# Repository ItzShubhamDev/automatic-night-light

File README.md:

# Auto Night Light

An set of automatic lights that turns on and off automatically according to environment lighting.

## Schematic

## PCB

## 3D Images

## Bill Of Materials

| Name                 | Quantity |
| -------------------- | -------- |
| Battery Cell CR2032  | 1        |
| LED 5mm              | 5        |
| Transistor 2N3904    | 1        |
| Photoresistor GL5528 | 1        |
| Resistor 220Ω        | 1        |
| Resistor 47kΩ        | 1        |
| Push Button 6mm      | 1        |

Made by [@Shubham](https://hackclub.slack.com/team/U07FW3J47ME)!

Made as a part of [Solder YSWS](http://solder.hackclub.com/)!

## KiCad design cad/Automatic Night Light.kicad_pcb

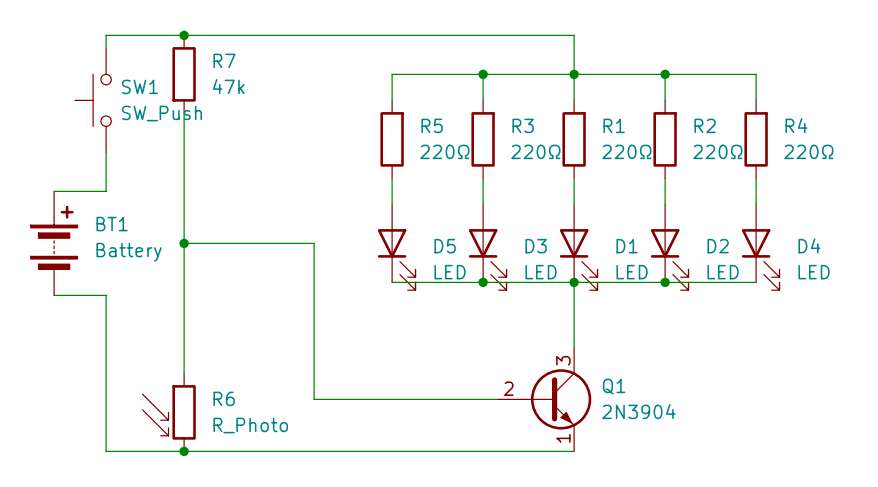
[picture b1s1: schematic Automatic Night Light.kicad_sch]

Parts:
BT1: Battery; BatteryHolder_Keystone_3034_1x20mm
D1, D2, D3, D4, D5: LED; LED_D5.0mm
Q1: 2N3904; TO-92_Inline
R1, R2, R3, R4, R5: 220Ω; R_Axial_DIN0207_L6.3mm_D2.5mm_P7.62mm_Horizontal
R6: R_Photo; R_LDR_7x6mm_P5.1mm_Vertical
R7: 47k; R_Axial_DIN0207_L6.3mm_D2.5mm_P7.62mm_Horizontal
SW1: SW_Push; SW_PUSH_6mm

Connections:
unnamed: BT1.1 (+), SW1.1
unnamed: BT1.2 (-), Q1.1 (E), R6.2
unnamed: D1.2 (A), R1.1
unnamed: D1.1 (K), D2.1 (K), D3.1 (K), D4.1 (K), D5.1 (K), Q1.3 (C)
unnamed: D2.2 (A), R2.1
unnamed: D3.2 (A), R3.1
unnamed: D4.2 (A), R4.1
unnamed: D5.2 (A), R5.1
unnamed: Q1.2 (B), R6.1, R7.2
unnamed: R1.2, R2.2, R3.2, R4.2, R5.2, R7.1, SW1.2

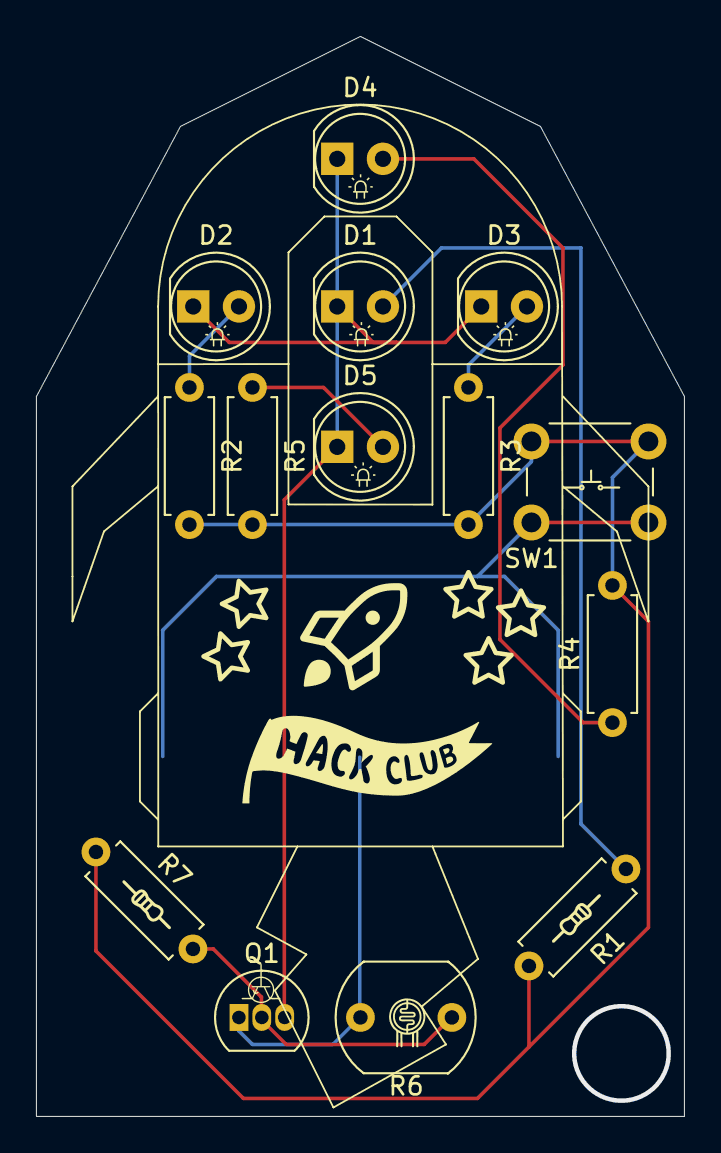
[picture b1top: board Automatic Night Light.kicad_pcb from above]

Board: 2 copper layers, 36.0 x 60.0 mm, 15 parts (1 on the bottom side), 10 nets.

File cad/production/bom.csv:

Designator,Footprint,Quantity,Value,LCSC Part #
BT1,BatteryHolder_Keystone_3034_1x20mm,1,Battery,
"D1, D2, D3, D4, D5",LED_D5.0mm,5,LED,
Q1,TO-92_Inline,1,2N3904,
"R1, R2, R3, R4, R5",R_Axial_DIN0207_L6.3mm_D2.5mm_P7.62mm_Horizontal,5,220Ω,
R6,R_LDR_7x6mm_P5.1mm_Vertical,1,R_Photo,
R7,R_Axial_DIN0207_L6.3mm_D2.5mm_P7.62mm_Horizontal,1,47k,
SW1,SW_PUSH_6mm,1,SW_Push,

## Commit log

2025-07-01 Upload Project Files
2025-07-02 Update PCB
2025-07-02 Update PCB Image
2025-07-03 Add separate resistors for LEDs
